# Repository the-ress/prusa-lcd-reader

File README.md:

# Prusa LCD Reader

Connects to flat ribbon cable no. 1 of Prusa MK3S or similar, listens to LCD
communication, and sends the text to Home Assistant.

## How it looks

## Preparing the printer

Get a [10-pin IDC connector](https://www2.mouser.com/ProductDetail/Wurth-Elektronik/61201023021?qs=W%252B2sBeLta1Y7QgcPlTMBZQ%3D%3D)
and carefully attach it to flat ribbon cable no. 1, approximately where you want
the device to go. Make sure the orientation matches the other connectors.

## Manufacturing notes

The board design doesn't rely on plated through-holes for the headers. (It still needs
some vias though.)

If you have the board manufactured profesionally, add some vias under pad 39 of
the ESP for better thermal performance.

### Components

- ESP32-WROOM-32
- voltage regulator 5V to 3.3V - SOT-233-3 footprint
- 6 NPN transistors (to protect GPIO from 5V signal) - SOT-23-3 footprint
- various resistors and capacitors - 0805 footprint
- 10-pin IDC connector header
- a reset button (optional)
- additional pin headers for the initial flashing (optional if you can bodge the
  connection without them)

## Sample ESPHome configuration
```yaml
external_components:
  - source: github://the-ress/prusa-lcd-reader@main
    components:
      - prusa_lcd

prusa_lcd:
  data_pins:
    - GPIO21
    - GPIO17
    - GPIO22
    - GPIO16
  enable_pin: GPIO19
  rs_pin: GPIO18
  text_sensors:
    - name: "Line 1"
    - name: "Line 2"
    - name: "Line 3"
    - name: "Line 4"
```

## Sample Lovelace card
````yaml
type: markdown
content: |-
  ```
  {{ states('sensor.printer_lcd_line_1') }}
  {{ states('sensor.printer_lcd_line_2') }}
  {{ states('sensor.printer_lcd_line_3') }}
  {{ states('sensor.printer_lcd_line_4') }}
  ```
````

## Resources
- Decoder code adapted from https://github.com/fsalomon/HD44780-decoder/
- Special characters mapping: https://github.com/prusa3d/Prusa-Firmware/blob/MK3/Firmware/lcd.h#L199
- LCD board docs: https://reprap.org/wiki/RepRapDiscount_Smart_Controller
- Printer main board schematic: https://github.com/ultimachine/Einsy-Rambo/blob/1.1a/board/Project%20Outputs/Schematic%20Prints_Einsy%20Rambo_1.1a.PDF

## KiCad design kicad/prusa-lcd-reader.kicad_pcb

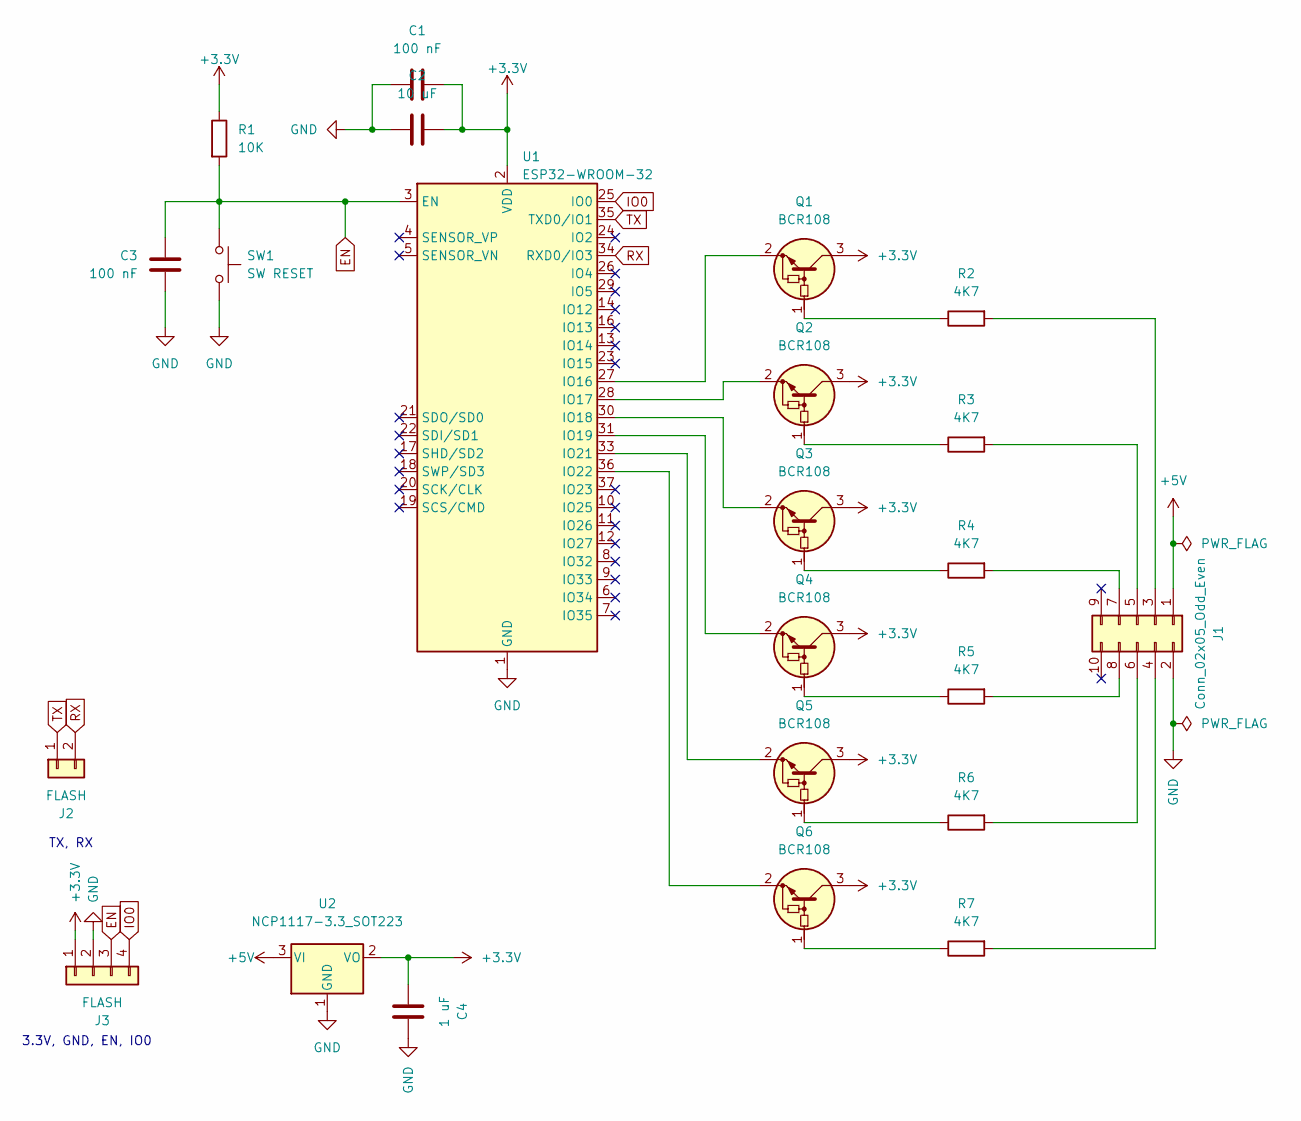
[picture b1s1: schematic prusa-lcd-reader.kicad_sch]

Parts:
C1, C3: 100 nF; C_0805_2012Metric
C2: 10 uF; C_0805_2012Metric
C4: 1 uF; C_0805_2012Metric
J1: Conn_02x05_Odd_Even
J2: FLASH; PinHeader_1x02_P2.54mm_Vertical
J3: FLASH; PinHeader_1x04_P2.54mm_Vertical
Q1, Q2, Q3, Q4, Q5, Q6: BCR108; SOT-23
R1: 10K; R_0805_2012Metric
R2, R3, R4, R5, R6, R7: 4K7; R_0805_2012Metric
SW1: SW RESET; SW_Push_TD-03XA-T
U1: ESP32-WROOM-32
U2: NCP1117-3.3_SOT223; SOT-223-3_TabPin2

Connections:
+3.3V: C1.2, C2.2, C4.1, J3.1, Q1.3 (C), Q2.3 (C), Q3.3 (C), Q4.3 (C), Q5.3 (C), Q6.3 (C), R1.1, U1.2 (VDD), U2.2 (VO)
+5V: J1.1, U2.3 (VI)
EN: C3.1, J3.3, R1.2, SW1.1, U1.3 (EN)
GND: C1.1, C2.1, C3.2, C4.2, J1.2, J3.2, SW1.2, U1.1 (GND), U1.15 (GND), U1.38 (GND), U1.39 (GND), U2.1 (GND)
IO0: J3.4, U1.25 (IO0)
unnamed: J1.3, R2.2
unnamed: J1.4, R7.2
unnamed: J1.5, R3.2
unnamed: J1.6, R6.2
unnamed: J1.7, R4.2
unnamed: J1.8, R5.2
unnamed: Q1.1 (B), R2.1
unnamed: Q1.2 (E), U1.27 (IO16)
unnamed: Q2.1 (B), R3.1
unnamed: Q2.2 (E), U1.28 (IO17)
unnamed: Q3.1 (B), R4.1
unnamed: Q3.2 (E), U1.30 (IO18)
unnamed: Q4.1 (B), R5.1
unnamed: Q4.2 (E), U1.31 (IO19)
unnamed: Q5.1 (B), R6.1
unnamed: Q5.2 (E), U1.33 (IO21)
unnamed: Q6.1 (B), R7.1
unnamed: Q6.2 (E), U1.36 (IO22)
RX: J2.2, U1.34 (RXD0/IO3)
TX: J2.1, U1.35 (TXD0/IO1)

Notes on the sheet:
3.3V, GND, EN, IO0
TX, RX

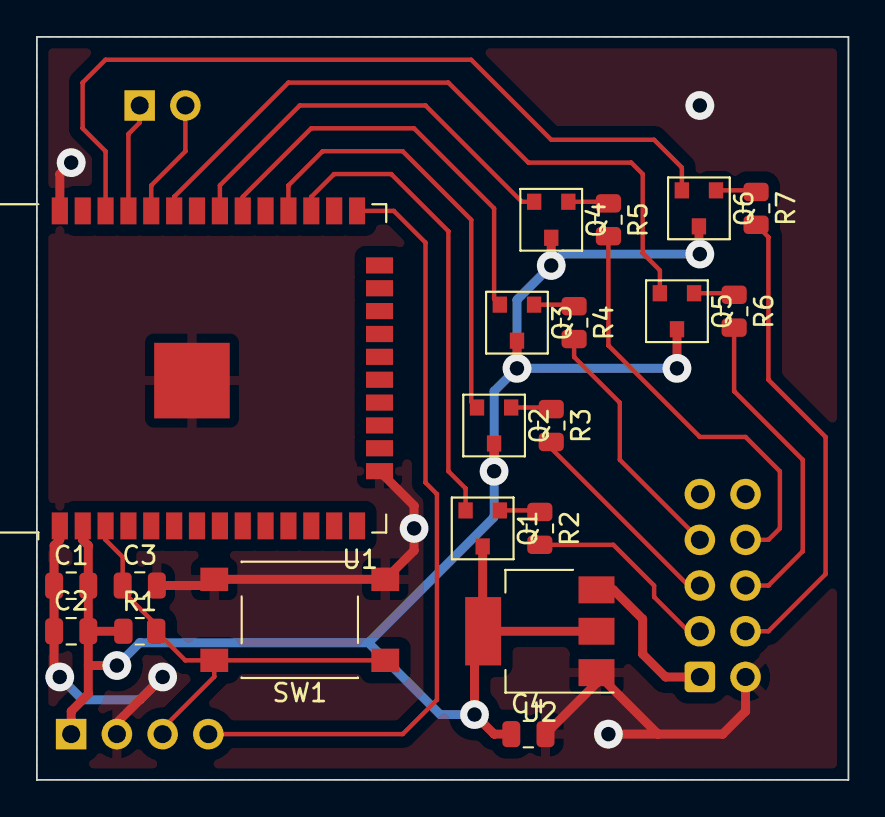
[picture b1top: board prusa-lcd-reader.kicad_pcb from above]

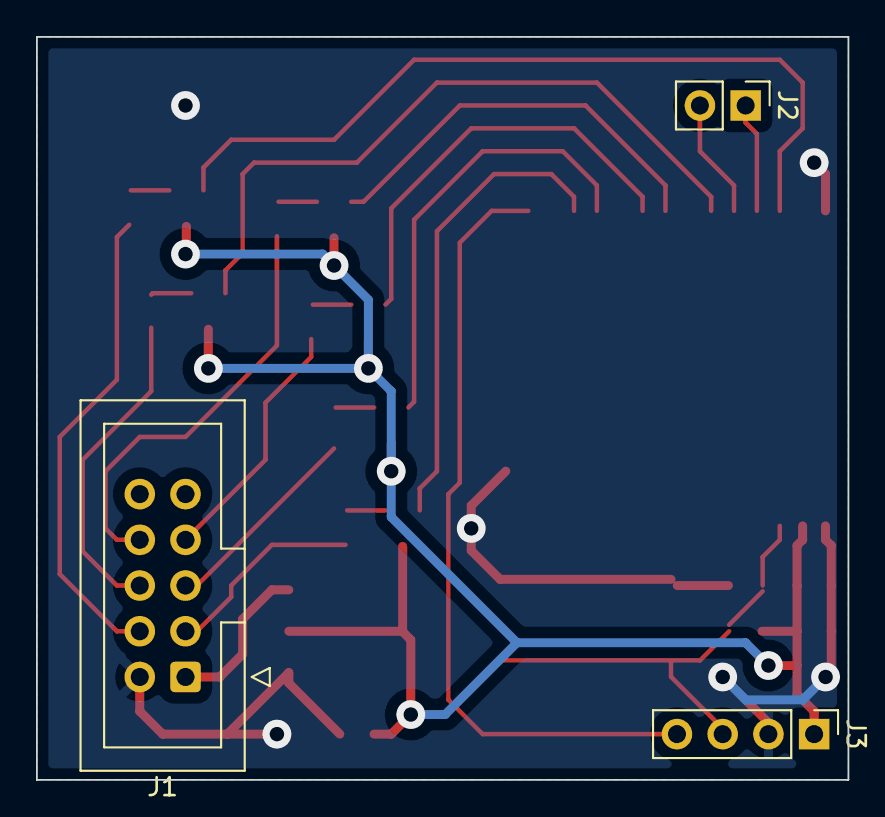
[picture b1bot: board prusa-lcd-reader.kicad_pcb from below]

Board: 2 copper layers, 45.1 x 41.3 mm, 23 parts (3 on the bottom side), 25 nets.

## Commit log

2023-03-23 Add existing code
2023-03-24 Write down readme
2023-03-24 Add images and sample lovelace card
